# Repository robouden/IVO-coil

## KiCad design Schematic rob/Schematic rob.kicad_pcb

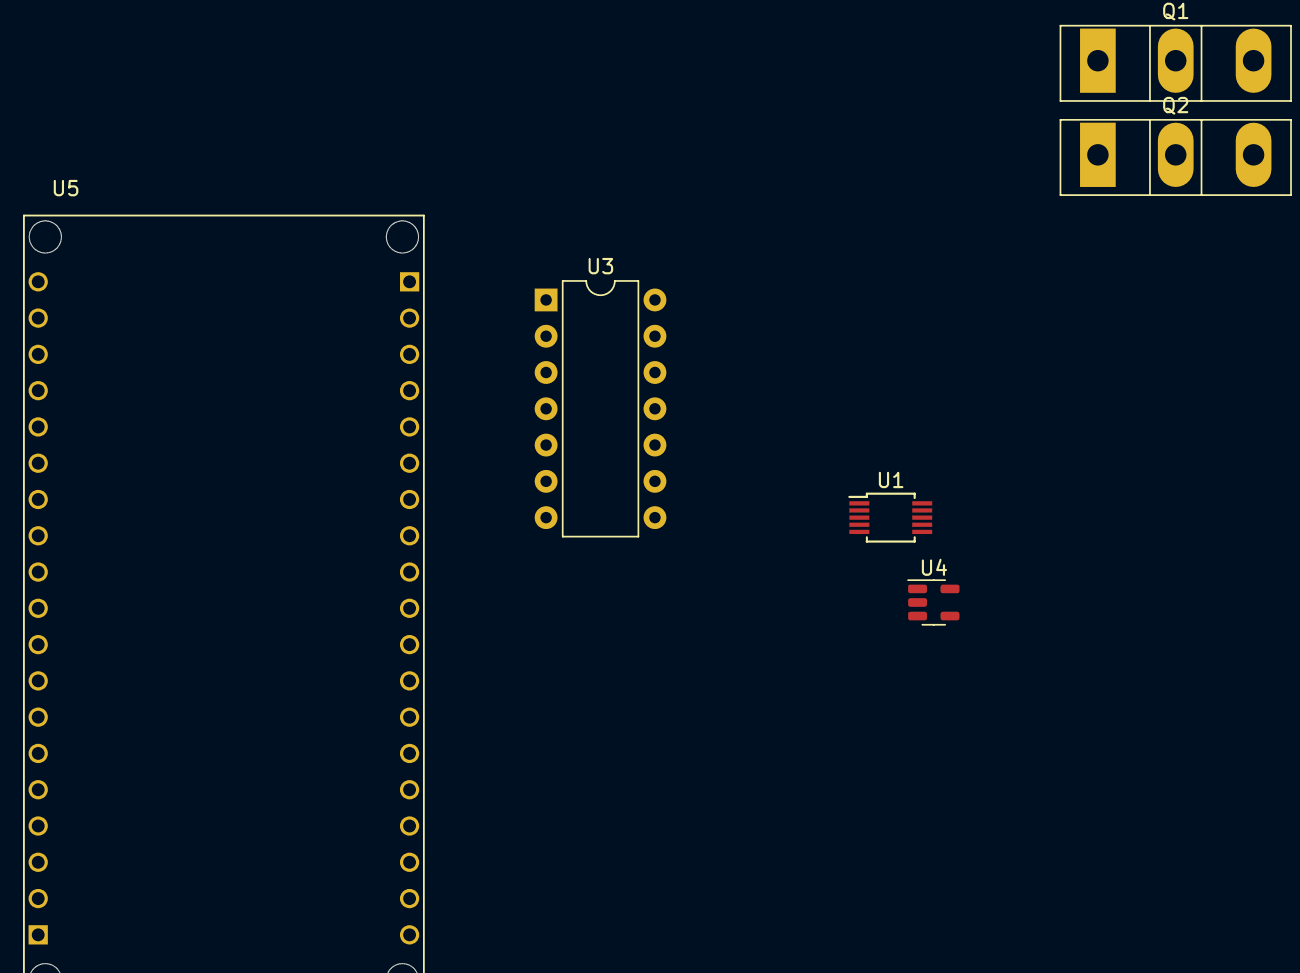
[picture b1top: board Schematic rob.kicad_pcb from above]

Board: 2 copper layers, 6 parts (0 on the bottom side), 6 nets, no tracks yet.

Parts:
Q1, Q2: C2M0160120D or C2M0080120D; TO-247-3_Vertical
U1: Si5351A-B-GT; MSOP-10_3x3mm_P0.5mm
U3: IR2213; DIP-14_W7.62mm
U4: SSD1306; SOT-23-5
U5: ESP32_NODEMCU; MODULE_ESP32_NODEMCU

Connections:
Earth: U3.2 (COM), U3.13 (VSS), U4.1 (GND), U5.J5_6 (GND_J5_6)
unnamed: Q1.3 (S), Q2.2 (D)
unnamed: U1.4 (SCL), U4.3 (SCL)
unnamed: U1.5 (SDA), U4.4 (SDA), U5.J4_3 (G22), U5.J4_6 (G21), U5.J5_11 (G25)
unnamed: U1.1 (VDD), U3.9 (VDD), U5.J5_19 (3V3)
unnamed: U3.10 (HIN), U3.12 (LIN)

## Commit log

2023-06-02 Init
2023-06-10 Updated schematic and added datasheets
2023-06-11 updated schematic
2023-06-11 Code for rotay encoder
2023-06-12 Updated schematic and extra docs
2023-06-25 updated board data
